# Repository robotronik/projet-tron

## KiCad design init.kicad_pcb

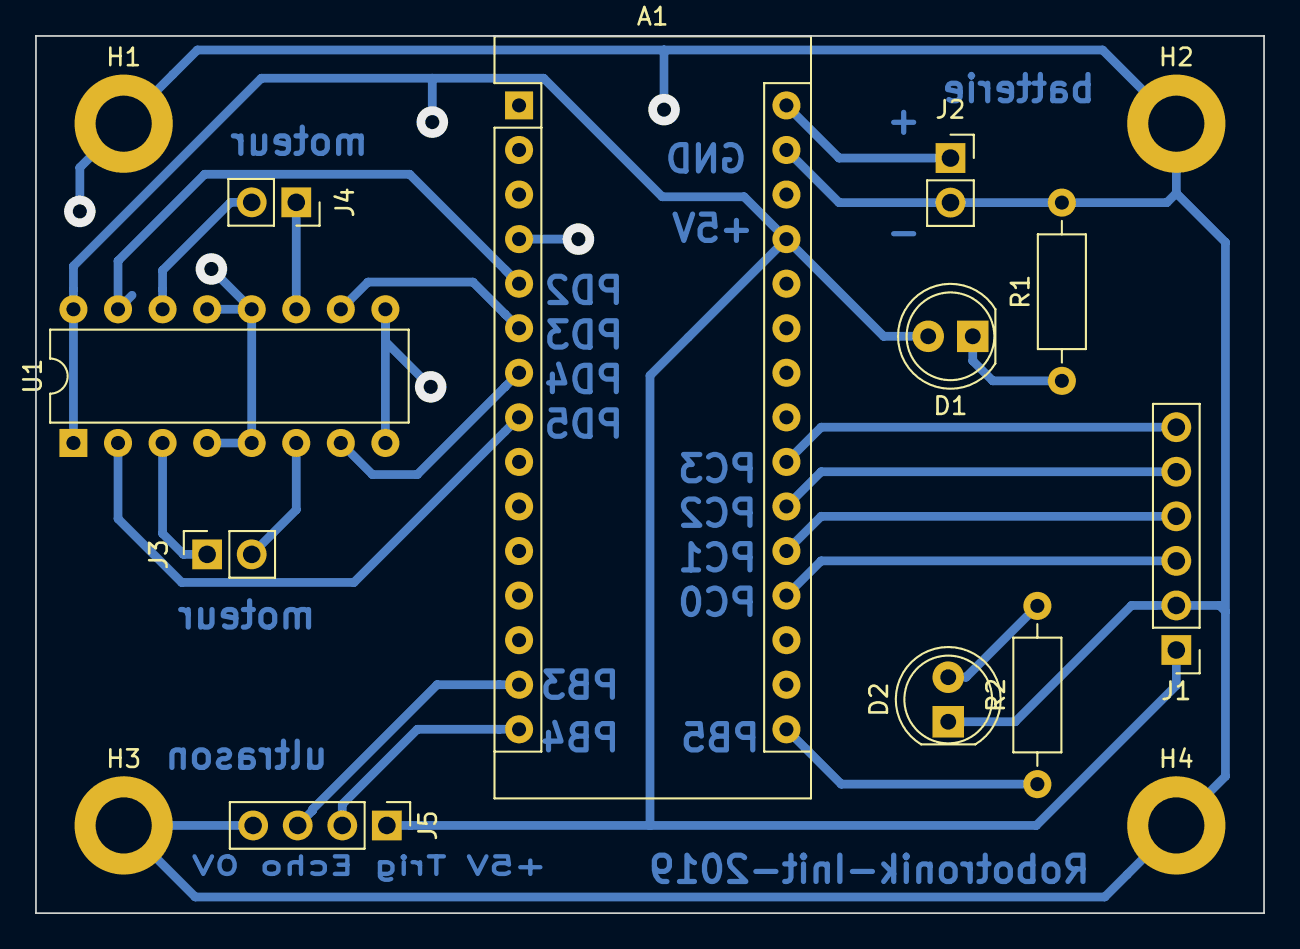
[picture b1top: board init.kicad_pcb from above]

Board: 2 copper layers, 70.0 x 50.0 mm, 15 parts (0 on the bottom side), 20 nets.

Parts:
A1: Arduino_Nano_v3.x; Arduino_Nano
D1: LED_verte; LED_D5.0mm
D2: LED_rouge; LED_D5.0mm
H1, H2, H3, H4: MountingHole_Pad; MountingHole_3.2mm_M3_DIN965_Pad
J1: Conn_01x06_Male; PinHeader_1x06_P2.54mm_Vertical
J2: Conn_01x02_Male; PinSocket_1x02_P2.54mm_Vertical
J3, J4: Conn_01x02_Female; PinSocket_1x02_P2.54mm_Vertical
J5: Conn_01x04_Female; PinHeader_1x04_P2.54mm_Vertical
R1, R2: 470; R_Axial_DIN0207_L6.3mm_D2.5mm_P10.16mm_Horizontal
U1: L293D; DIP-16_W7.62mm

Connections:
+5V: A1.27, D1.2, J1.1, J5.1, U1.1, U1.8, U1.9, U1.16
+BATT: A1.30, J2.1
C1: A1.19, J1.3
C2: A1.20, J1.4
C3: A1.21, J1.5
C4: A1.22, J1.6
Echo: A1.14, J5.3
GND: A1.4, A1.29, D2.1, H1.1, H2.1, H3.1, H4.1, J1.2, J2.2, J5.4, R1.2, U1.4, U1.5, U1.12, U1.13
unnamed: A1.16, R2.1
unnamed: D1.1, R1.1
unnamed: D2.2, R2.2
unnamed: J3.1, U1.3
unnamed: J3.2, U1.6
unnamed: J4.1, U1.11
unnamed: J4.2, U1.14
O1: A1.7, U1.7
O2: A1.5, U1.15
PWM1: A1.8, U1.2
PWM2: A1.6, U1.10
Trig: A1.15, J5.2

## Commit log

2019-09-26 commit initial, lancement du projet
2019-09-27 ajout stl support front
2019-10-02 ajout PCB Arduino/Moteur
2019-10-02 retour
2019-10-02 ajout PCB Main
2019-10-02 ajout du tuto fusion
2019-10-02 tutofusionpdf
2019-10-02 Im a clown
2019-10-03 modif du routage
